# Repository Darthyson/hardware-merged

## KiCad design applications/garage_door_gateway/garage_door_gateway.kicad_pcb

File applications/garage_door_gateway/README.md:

# Garage Door Gateway

KNX-Modul für den Hörmann Supramatic E3 (E2) Garagentorantrieb.  
KNX-module for the Hoermann Supramatic E3 (E2) garage door opener.

### Requirements

- Controller: [TS_ARM](../../modules_lpc1115_fm/ts_arm)  
- Firmware: [HoermannGateway](https://github.com/selfbus/software-arm-incubation/tree/main/misc/HoermannGateway)

### Inspired by:  
- https://blog.bouni.de/posts/2018/hoerrmann-uap1
- https://github.com/stephan192/hoermann_door

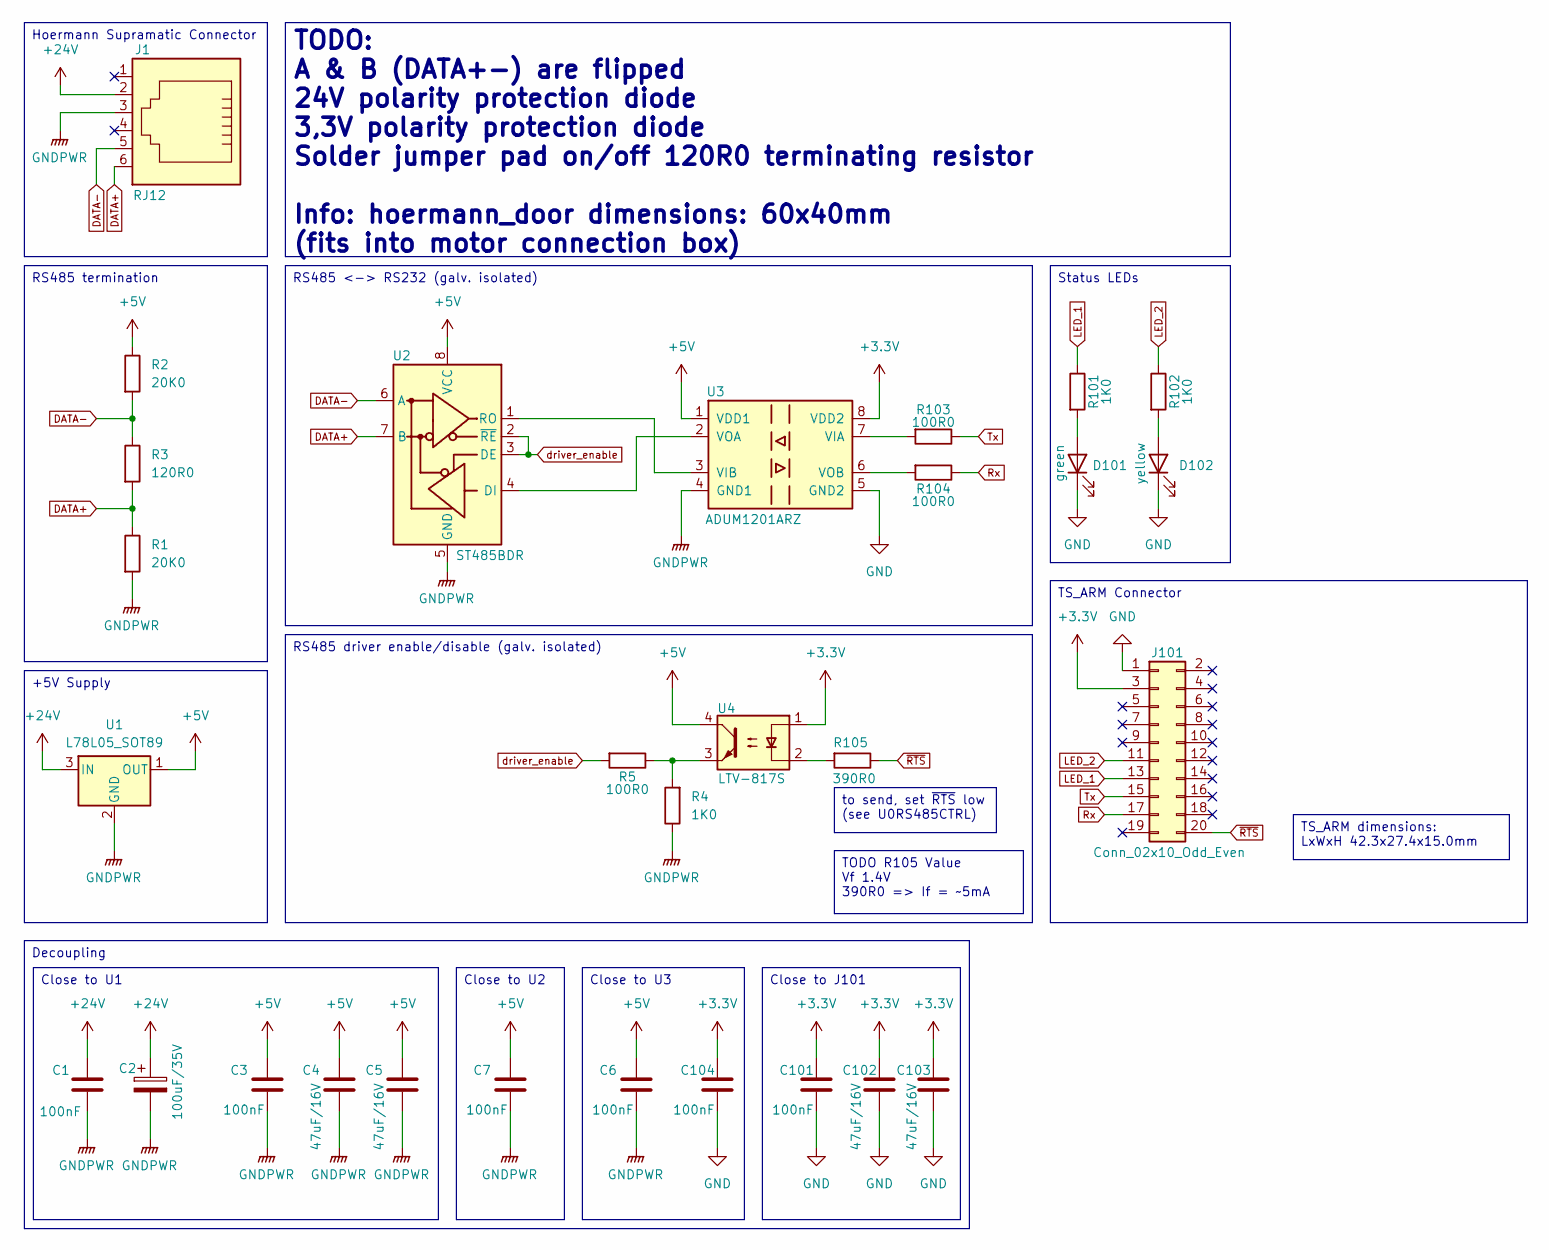
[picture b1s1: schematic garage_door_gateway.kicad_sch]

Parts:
C1, C3, C6, C7, C101, C104: 100nF; C_0805_2012Metric
C2: 100uF/35V; CP_Elec_6.3x7.7
C4, C5, C102, C103: 47uF/16V; C_1206_3216Metric_Pad1.33x1.80mm_HandSolder
D101: green; LED_1206_3216Metric
D102: yellow; LED_1206_3216Metric
J1: RJ12; RJ12_MEBP 6-6S-x06_Horizontal
J101: Conn_02x10_Odd_Even; PinHeader_2x10_P2.54mm_Horizontal
R1, R2: 20K0; R_0805_2012Metric
R3: 120R0; R_0805_2012Metric
R4, R101, R102: 1K0; R_0805_2012Metric
R5, R103, R104: 100R0; R_0805_2012Metric
R105: 390R0; R_0805_2012Metric
U1: L78L05_SOT89; SOT-89-3
U2: ST485BDR; SOIC-8_3.9x4.9mm_P1.27mm
U3: ADUM1201ARZ; SOIC-8_3.9x4.9mm_P1.27mm_isolated_4mm
U4: LTV-817S; SMDIP-4_W9.53mm

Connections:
+3.3V: C101.1, C102.1, C103.1, C104.1, J101.3, U3.8 (VDD2), U4.1
+5V: C3.1, C4.1, C5.1, C6.1, C7.1, R2.1, U1.1 (OUT), U2.8 (VCC), U3.1 (VDD1), U4.4
+24V: C1.1, C2.1, J1.2, U1.3 (IN)
DATA+: J1.6, R1.1, R3.2, U2.7 (B)
DATA-: J1.5, R2.2, R3.1, U2.6 (A)
GND: C101.2, C102.2, C103.2, C104.2, D101.1 (K), D102.1 (K), J101.1, U3.5 (GND2)
GNDPWR: C1.2, C2.2, C3.2, C4.2, C5.2, C6.2, C7.2, J1.3, R1.2, R4.1, U1.2 (GND), U2.5 (GND), U3.4 (GND1)
LED_1: J101.13, R101.1
LED_2: J101.11, R102.1
unnamed: D101.2 (A), R101.2
unnamed: D102.2 (A), R102.2
unnamed: R4.2, R5.1, U4.3
unnamed: R105.2, U4.2
unnamed: U2.4 (DI), U3.2 (VOA)
unnamed: U2.1 (RO), U3.3 (VIB)
unnamed: R103.2, U3.7 (VIA)
unnamed: R104.2, U3.6 (VOB)
Rx: J101.17, R104.1
Tx: J101.15, R103.1
driver_enable: R5.2, U2.2 (~RE), U2.3 (DE)
~RTS: J101.20, R105.1

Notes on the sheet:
TODO: A & B (DATA+-) are flipped 24V polarity protection diode 3,3V polarity protection diode Solder jumper pad on/off 120R0 terminating resistor Info: hoermann_door dimensions: 60x40mm (fits into motor connection box)
RS485 termination
Close to U2
Close to J101
Status LEDs
RS485 driver enable/disable (galv. isolated)
Hoermann Supramatic Connector
TS_ARM dimensions: LxWxH 42.3x27.4x15.0mm
TODO R105 Value Vf 1.4V 390R0 => If = ~5mA
RS485 <-> RS232 (galv. isolated)
TS_ARM Connector
+5V Supply
Close to U1
Close to U3
Decoupling
to send, set ~{RTS} low (see U0RS485CTRL)

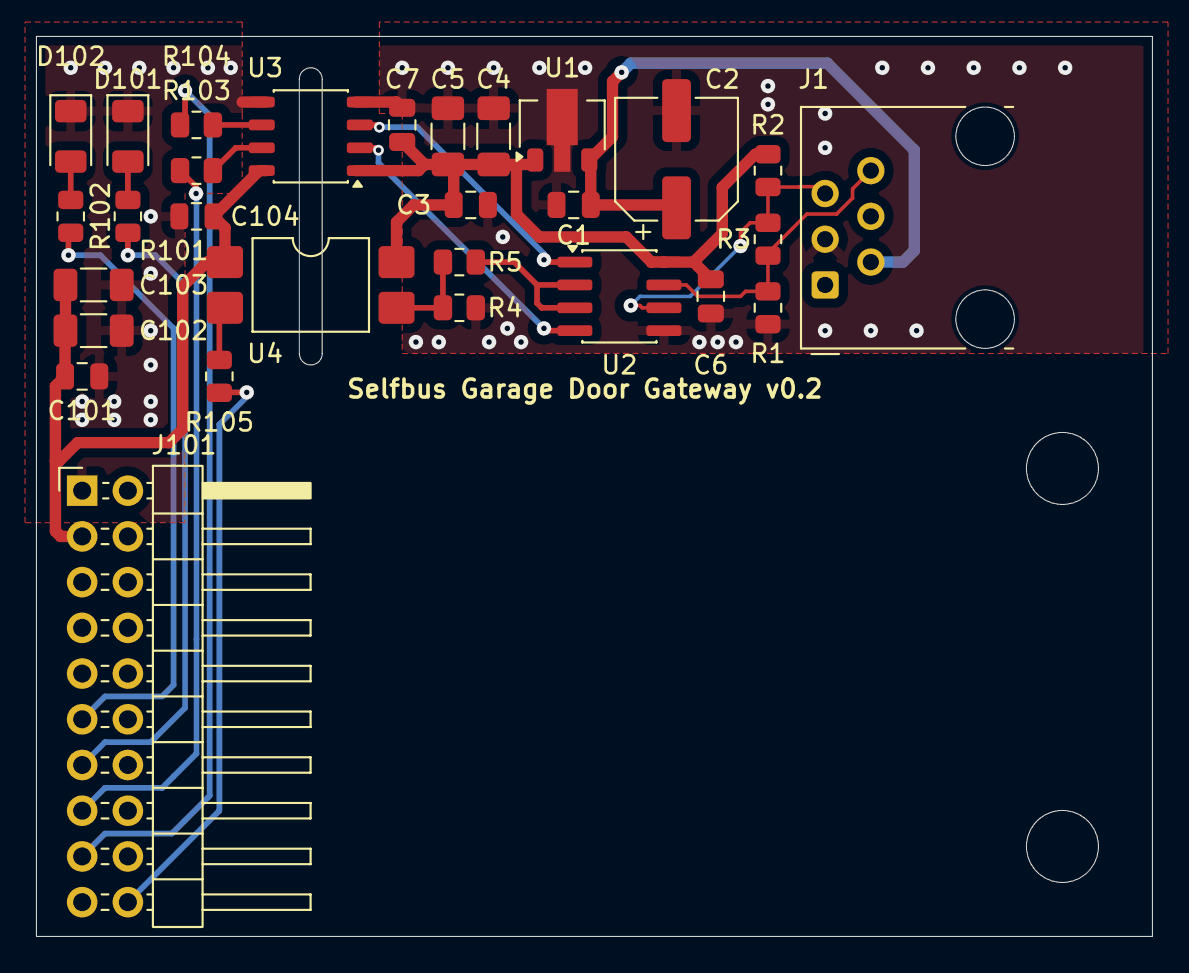
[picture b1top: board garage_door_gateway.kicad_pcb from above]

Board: 2 copper layers, 62.0 x 50.0 mm, 29 parts (0 on the bottom side), 21 nets.

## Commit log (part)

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2026-01-08 Header mapping file created.
2026-01-08 Bottom view mirrored.
2026-03-19 Add entries for KiCad files to `.gitignore`
2026-03-19 Move Raincenter to new application subfolder.
2026-03-19 [raincenter] Delete warning from README.md file
    The PCB has been working fine for me since late 2020.
2026-03-19 [garage_door_gateway] Initial commit
    New KNX-module for the Hoermann Supramatic E3 (E2) garage door opener.
    Basically a galvanic isolated rs485<->rs232 converter for the [TS_ARM](../../modules_lpc1115_fm/ts_arm)
